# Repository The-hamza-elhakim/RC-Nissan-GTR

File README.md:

# ENEL 300 RC Car – Embedded Systems Final Project

# RC-Nissan-GTR
RC Car modeled after the Iconic Nissan GTR r35. Designed from scratch using AVR128DB28 MCU, ultrasonic sensors, joystick control, I2C LCD, and L298N motor driver. Built in MPLAB X, with custom PCBs, bare-metal C firmware, and real-time sensor feedback.

## Overview
This project is a fully functional RC car built from scratch using embedded C on the AVR128DB28 microcontroller. It includes:

- motor control via custom built L298N motor driver PCB
- Ultrasonic sensor for obstacle detection
- 4 digit display for distance feedback
- Remote controller using joystick module (KY-023) and Wireless 433Mhz RF Transmitter/Receiver Modules
- Custom PCBs and real-time sensor integration

## Features
- Real-time distance sensing (HC-SR04)
- Metal detection with buzzer output
- Headlight control (GPIO driven)
- Directional motor control with PWM
- I2C LCD for debug/status

## Technologies
- AVR128DB28 microcontroller
- Bare-metal C (no Arduino)
- MPLAB X IDE
- I2C, PWM, ADC, GPIO
- Custom PCB Design (KiCAD)

## Documentation
See [`Documentation/`](Documentation/) folder for project reports and architecture

Read the full project report here:  
[ENEL 300 RC Car Final Report (Google Docs)](https://docs.google.com/document/d/1p-epSyup4PSlBaB8h3Y5LkGUN4icb1V6V-HfzxVr1pI/edit?tab=t.0)

## Author
Hamza Elhakim – Electrical and Computer Engineering Student

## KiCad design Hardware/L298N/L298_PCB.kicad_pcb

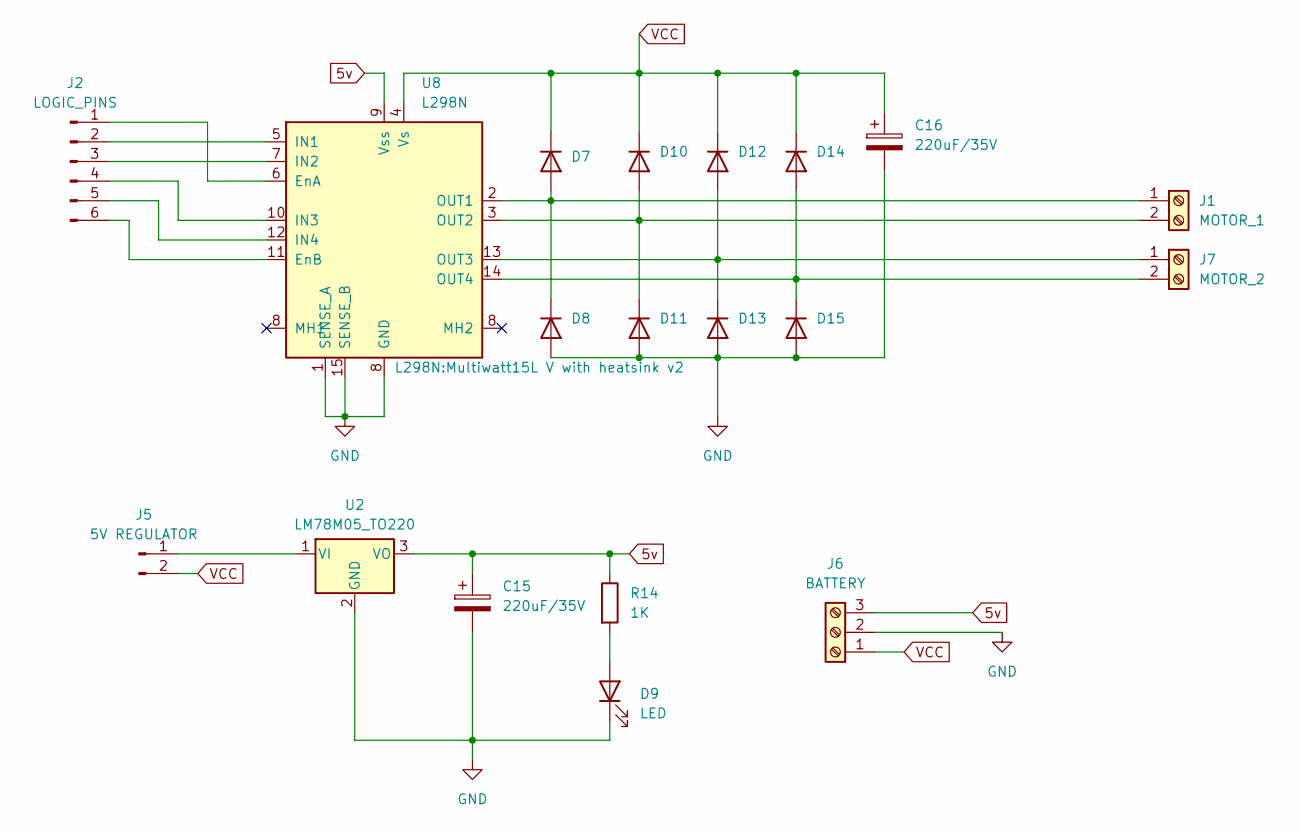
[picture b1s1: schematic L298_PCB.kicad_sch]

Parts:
C15, C16: 220uF/35V; C_Radial_D10.0mm_H16.0mm_P5.00mm
D7: D_A-405_P7.62mm_Horizontal
D8, D10, D11, D12, D13, D14, D15: .; D_A-405_P7.62mm_Horizontal
D9: LED; LED_D3.0mm
J1: MOTOR_1; TerminalBlock_Phoenix_MKDS-1,5-2-5.08_1x02_P5.08mm_Horizont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
J2: LOGIC_PINS; PinHeader_1x06_P2.54mm_Vertical
J5: 5V REGULATOR; PinHeader_1x02_P2.54mm_Vertical
J6: BATTERY; TerminalBlock_Phoenix_MKDS-1,5-3_1x03_P5.00mm_Horizontal
J7: MOTOR_2; TerminalBlock_Phoenix_MKDS-1,5-2-5.08_1x02_P5.08mm_Horizont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
R14: 1K; R_Axial_DIN0204_L3.6mm_D1.6mm_P7.62mm_Horizontal
U2: LM78M05_TO220; TO-220-3_Vertical
U8: L298N; Multiwatt15L V with heatsink v2

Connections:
5v: C15.1, J6.3, R14.1, U2.3 (VO), U8.9 (Vss)
GND: C15.2, C16.2, D8.2 (A), D9.1 (K), D11.2 (A), D13.2 (A), D15.2 (A), J6.2, U2.2 (GND), U8.1 (SENSE_A), U8.8 (GND), U8.15 (SENSE_B)
unnamed: D7.2 (A), D8.1 (K), J1.1, U8.2 (OUT1)
unnamed: D9.2 (A), R14.2
unnamed: D10.2 (A), D11.1 (K), J1.2, U8.3 (OUT2)
unnamed: D12.2 (A), D13.1 (K), J7.1, U8.13 (OUT3)
unnamed: D14.2 (A), D15.1 (K), J7.2, U8.14 (OUT4)
unnamed: J2.1, U8.6 (EnA)
unnamed: J2.2, U8.5 (IN1)
unnamed: J2.3, U8.7 (IN2)
unnamed: J2.4, U8.10 (IN3)
unnamed: J2.5, U8.12 (IN4)
unnamed: J2.6, U8.11 (EnB)
unnamed: J5.1, U2.1 (VI)
VCC: C16.1, D7.1 (K), D10.1 (K), D12.1 (K), D14.1 (K), J5.2, J6.1, U8.4 (Vs)

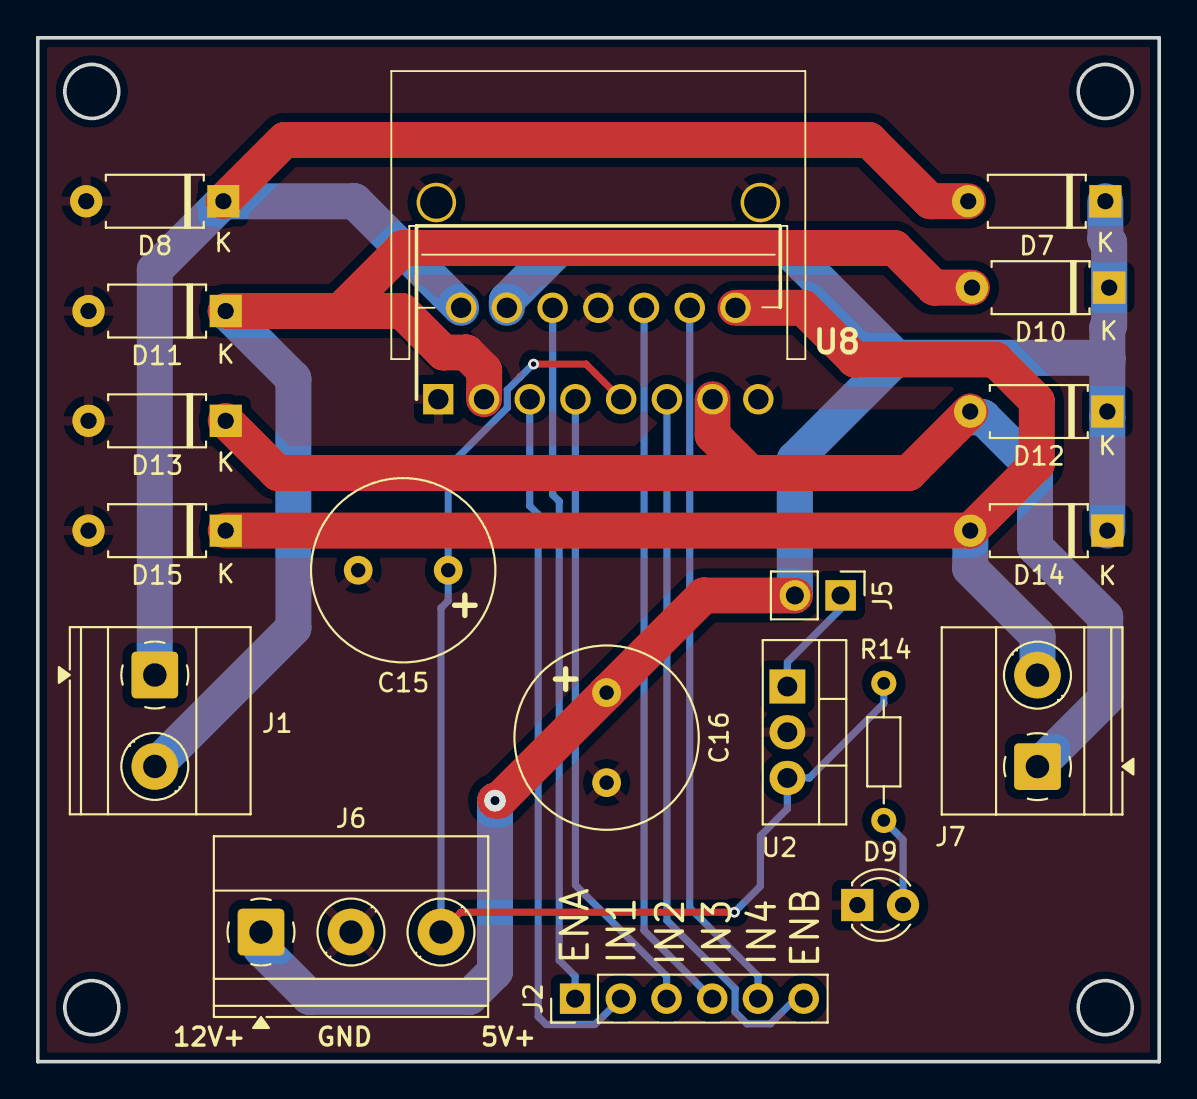
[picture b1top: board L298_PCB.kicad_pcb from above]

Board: 2 copper layers, 62.3 x 56.9 mm, 19 parts (0 on the bottom side), 15 nets.

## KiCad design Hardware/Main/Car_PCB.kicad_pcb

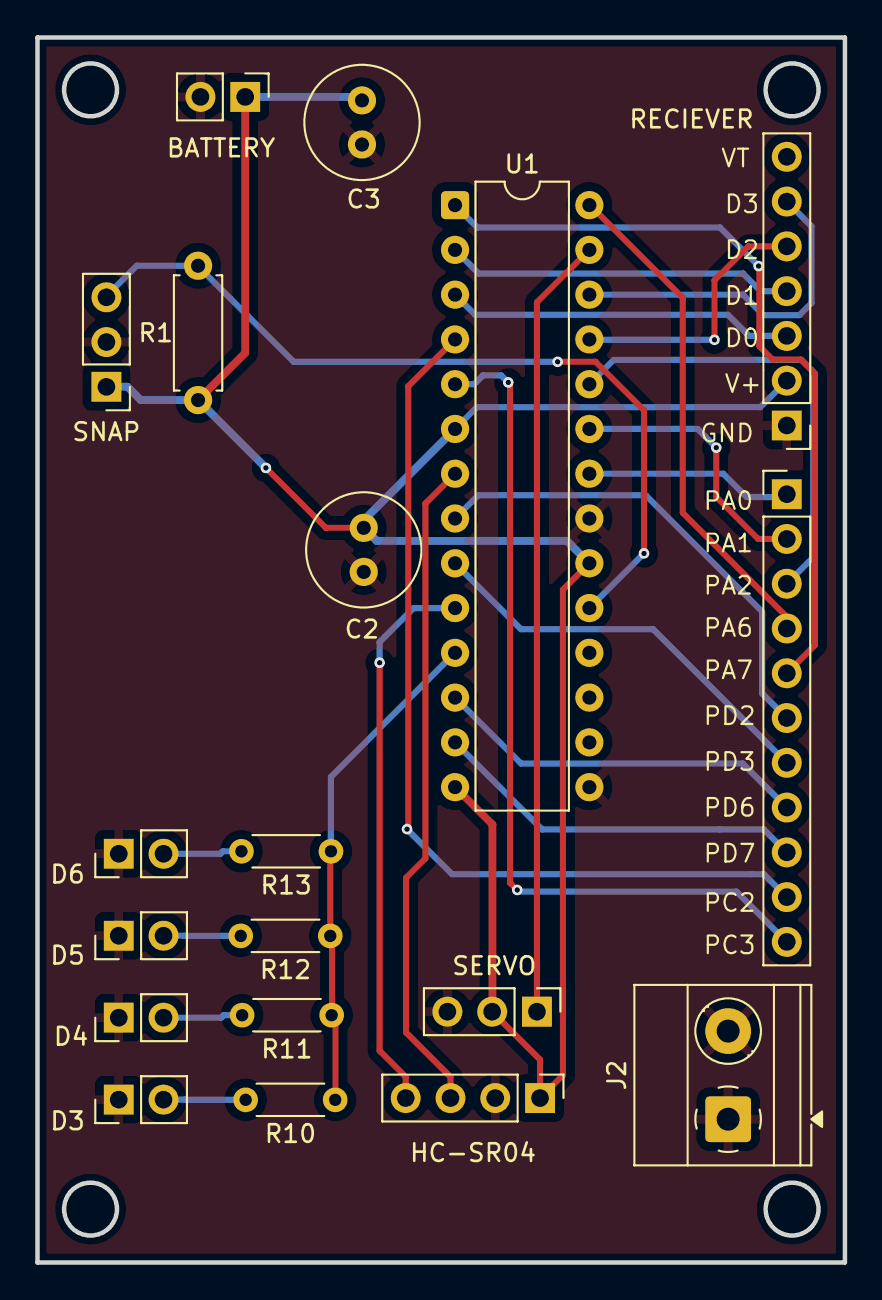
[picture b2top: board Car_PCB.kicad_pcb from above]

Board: 2 copper layers, 45.8 x 69.5 mm, 19 parts (0 on the bottom side), 26 nets.

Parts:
BATTERY: BATTERY; PinHeader_1x02_P2.54mm_Vertical
C2, C3: 1uF; C_Radial_D6.3mm_H5.0mm_P2.50mm
D3, D4, D5, D6: LED; PinHeader_1x02_P2.54mm_Vertical
HC-SR04: HC-SR04; PinHeader_1x04_P2.54mm_Vertical
J2: COMMON GND; TerminalBlock_Phoenix_MKDS-1,5-2_1x02_P5.00mm_Horizontal
J3: SPARE_PINS; PinHeader_1x11_P2.54mm_Vertical
R1: 1.2K; R_Axial_DIN0207_L6.3mm_D2.5mm_P7.62mm_Horizontal
R10, R11, R12, R13: 120; R_Axial_DIN0204_L3.6mm_D1.6mm_P5.08mm_Horizontal
RECIEVER: RX480-E4; PinHeader_1x07_P2.54mm_Vertical
SERVO: Motor_Servo; PinHeader_1x03_P2.54mm_Vertical
SNAP: SNAP PROGRAMER; PinHeader_1x03_P2.54mm_Vertical
U1: AVR128DB28x-xSP; DIP-28_W7.62mm

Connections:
5V: BATTERY.1, C2.1, C3.1, HC-SR04.1 (VCC), R1.1, RECIEVER.2, SERVO.2 (+), SNAP.1, U1.6 (VDDIO2), U1.14 (AVDD), U1.20 (VDD)
D0: RECIEVER.3, U1.3 (PC1)
D1: RECIEVER.4, U1.2 (PC0)
D2: RECIEVER.5, U1.25 (PA3)
D3: RECIEVER.6, U1.26 (PA4)
GND: BATTERY.2, C2.2, C3.2, D3.1 (K), D4.1 (K), D5.1 (K), D6.1 (K), HC-SR04.2 (GND), J2.1, J2.2, RECIEVER.1, SERVO.3 (-), SNAP.2, U1.15 (AGND), U1.21 (GND)
LED_SIG: R10.1, R11.1, R12.1, R13.1, U1.11 (PD5)
unnamed: D3.2 (A), R10.2
unnamed: D4.2 (A), R11.2
unnamed: D5.2 (A), R12.2
unnamed: D6.2 (A), R13.2
unnamed: R1.2, SNAP.3, U1.19 (UPDI)
PA0: J3.1, U1.22 (XTALHF1/PA0)
PA1: J3.2, U1.23 (XTALHF2/PA1)
PA2: J3.3, U1.24 (PA2)
PA6: J3.4, U1.28 (PA6)
PA7: J3.5, U1.1 (PA7)
PC2: J3.10, U1.4 (PC2)
PC3: J3.11, U1.5 (PC3)
PD2: J3.6, U1.8 (PD2)
PD3: J3.7, U1.9 (PD3)
PD6: J3.8, U1.12 (PD6)
PD7: J3.9, U1.13 (VREFA/PD7)
SERVO_SIG: SERVO.1 (PWM), U1.27 (PA5)
ULTRASONIC_ECHO: HC-SR04.4 (ECHO), U1.10 (PD4)
ULTRASONIC_TRIG: HC-SR04.3 (TRIG), U1.7 (PD1)

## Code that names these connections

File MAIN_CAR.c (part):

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#include <stdbool.h>

// === Pin Definitions ===
#define TM1637_CLK_PIN 7 // PD7
#define TM1637_DIO_PIN 6 // PD6
#define TM1637_PORT PORTD

#define HC_SR04_TRIG_PIN 1 // PD1
#define HC_SR04_ECHO_PIN 4 // PD4

#define MOTOR_ENA_PIN 0  // PA0 (PWM)
#define MOTOR_IN1_PIN 1  // PA1
#define MOTOR_IN2_PIN 2  // PA2
#define MOTOR_PORT PORTA

#define RF_FORWARD_MOTOR_PIN 0   // PC0
#define RF_BACKWARDS_MOTOR_PIN 1 // PC1
#define RF_PORT PORTC

#define SERVO_RIGHT_PIN 3 // PA3
#define SERVO_LEFT_PIN 4 // PA4
#define SERVO_PWM_PIN 5 // PA5
#define SERVO_PORT PORTA


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#define TM1637_CMD_SET_ADDR 0xC0
#define TM1637_CMD_DISPLAY_CTRL 0x88

#define METAL_INPUT_PIN   PIN6_bm   // PA6 input from metal detector
#define BUZZER_OUTPUT_PIN PIN2_bm   // PD2 output to buzzer
#define THRESHOLD_DIFF      1

#define SERVO_PWM_PIN 5      // PA5

// For 4MHz system clock
#define TIMER_PRESCALER      2       // Clock divider
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}

void rf_input_init(void) {
  // Set PA3, PA4 as inputs
  PORTC.DIRCLR = (1 << RF_FORWARD_MOTOR_PIN) | (1 << RF_BACKWARDS_MOTOR_PIN);

  // Enable internal pull-ups
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  PORTC.PIN5CTRL = PORT_PULLUPEN_bm;
  PORTC.PIN6CTRL = PORT_PULLUPEN_bm;
  
  // Set PA5, PA6 as inputs
  PORTA.DIRCLR = (1 << SERVO_RIGHT_PIN) | (1 << SERVO_LEFT_PIN);
  
  // Enable internal pull-ups
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// ===== METAL DETECTOR ===== //

void PORT_init(void) {
    // PA6: input from 555 timer
    PORTA.DIRCLR = METAL_INPUT_PIN;
    PORTA.PIN6CTRL = PORT_ISC_RISING_gc;  // Trigger ISR on rising edge

    // Optional: pull-down resistor for stability
    // PORTA.PIN6CTRL |= PORT_PULLUPEN_bm;

    // PD2: output to buzzer
    PORTD.DIRSET = BUZZER_OUTPUT_PIN;
    PORTD.OUTCLR = BUZZER_OUTPUT_PIN;
}
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  PORTD.DIRSET = (1 << TM1637_CLK_PIN) | (1 << TM1637_DIO_PIN) | (1 << HC_SR04_TRIG_PIN);
  PORTD.DIRCLR = (1 << HC_SR04_ECHO_PIN);
  PORTD.PIN4CTRL = PORT_PULLUPEN_bm | PORT_ISC_BOTHEDGES_gc;
  PORTD.DIRSET = (1 << 5) | (1 << 3);  // Set PD5 and PD3 as output

}

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
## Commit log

2025-05-07 Create temp
2025-05-07 Organizing some things
2025-05-07 hello
2025-05-07 deleted
